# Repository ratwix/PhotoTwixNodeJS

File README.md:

PhotoTwixNodeJS
===============

A NodeJS Photobooth, that embedded a DSP RX1 printer (optional) for 2x6 strip

Backend : NodeJS
Frontend : CSS / Javascript.
Compatible browser : Chrome
User interface : Arduino

*Install*

- Install nodejs
- Install nodejs module :
-- Canvas (be sure to have GTK bin in your path)
-- Express
-- Gyp
-- Johnny-five
-- winreg
-- copysync
-- fs-extra
-- fs-tools
-- json
-- ncp
-- optimist
-- path
-- static
-- body-parser

*Run*

node server.js
In chrome : https://localhost:1443

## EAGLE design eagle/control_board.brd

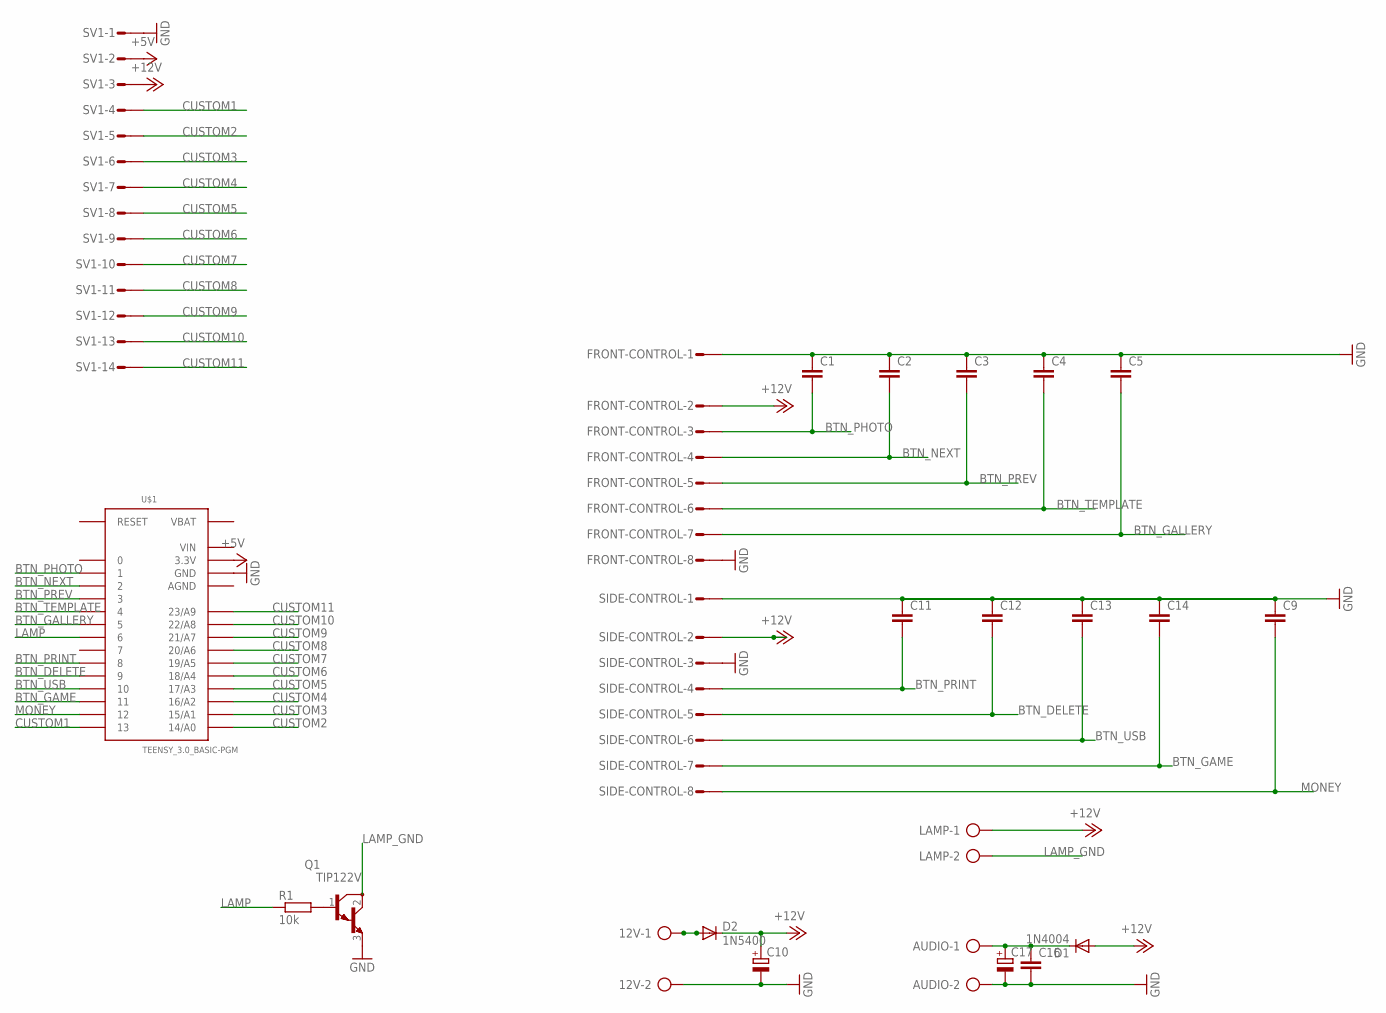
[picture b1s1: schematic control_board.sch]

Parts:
12V: AK300/2
AUDIO: AK300/2
C1, C2, C3, C4, C5, C9, C11, C12, C13, C14, C16: C-EU025-025X050; C025-025X050
C10: CPOL-EUE5-8.5; E5-8,5
C17: CPOL-EUE5-5; E5-5
D1: 1N4004; DO41-10
D2: 1N5400; DO201-15
FRONT-CONTROL: S08P
LAMP: AK300/2
Q1: TIP122V; TO220V
R1: 10k; 0204/7
SIDE-CONTROL: S08P
SV1: S14P
U$1: TEENSY_3.0_BASIC-PGM

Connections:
+5V: SV1.2, U$1.3.3V, U$1.3.3V1 (3.3V)
+12V: C10.+, D1.A, D2.C, FRONT-CONTROL.2, LAMP.1, SIDE-CONTROL.2, SV1.3
AGND: U$1.AGND
BTN_DELETE: C12.2, SIDE-CONTROL.5, U$1.9
BTN_GALLERY: C5.2, FRONT-CONTROL.7, U$1.5
BTN_GAME: C14.2, SIDE-CONTROL.7, U$1.11
BTN_NEXT: C2.2, FRONT-CONTROL.4, U$1.2
BTN_PHOTO: C1.2, FRONT-CONTROL.3, U$1.1
BTN_PREV: C3.2, FRONT-CONTROL.5, U$1.3
BTN_PRINT: C11.2, SIDE-CONTROL.4, U$1.8
BTN_TEMPLATE: C4.2, FRONT-CONTROL.6, U$1.4
BTN_USB: C13.2, SIDE-CONTROL.6, U$1.10
CUSTOM1: SV1.4, U$1.13
CUSTOM2: SV1.5, U$1.14/A0
CUSTOM3: SV1.6, U$1.15/A1
CUSTOM4: SV1.7, U$1.16/A2
CUSTOM5: SV1.8, U$1.17/A3
CUSTOM6: SV1.9, U$1.18/A4
CUSTOM7: SV1.10, U$1.19/A5
CUSTOM8: SV1.11, U$1.20/A6
CUSTOM9: SV1.12, U$1.21/A7
CUSTOM10: SV1.13, U$1.22/A8
CUSTOM11: SV1.14, U$1.23/A9
GND: 12V.2, AUDIO.2, C1.1, C2.1, C3.1, C4.1, C5.1, C9.1, C10.-, C11.1, C12.1, C13.1, C14.1, C16.2, C17.-, FRONT-CONTROL.1, FRONT-CONTROL.8, Q1.3 (E), SIDE-CONTROL.1, SIDE-CONTROL.3, SV1.1, U$1.GND, U$1.GND1 (GND)
LAMP: R1.1, U$1.6
LAMP_GND: LAMP.2, Q1.2 (C)
MONEY: C9.2, SIDE-CONTROL.8, U$1.12
unnamed: Q1.1 (B), R1.2
unnamed: AUDIO.1, C16.1, C17.+, D1.C
unnamed: 12V.1, D2.A
VBAT: U$1.VBAT
VIN: U$1.VIN

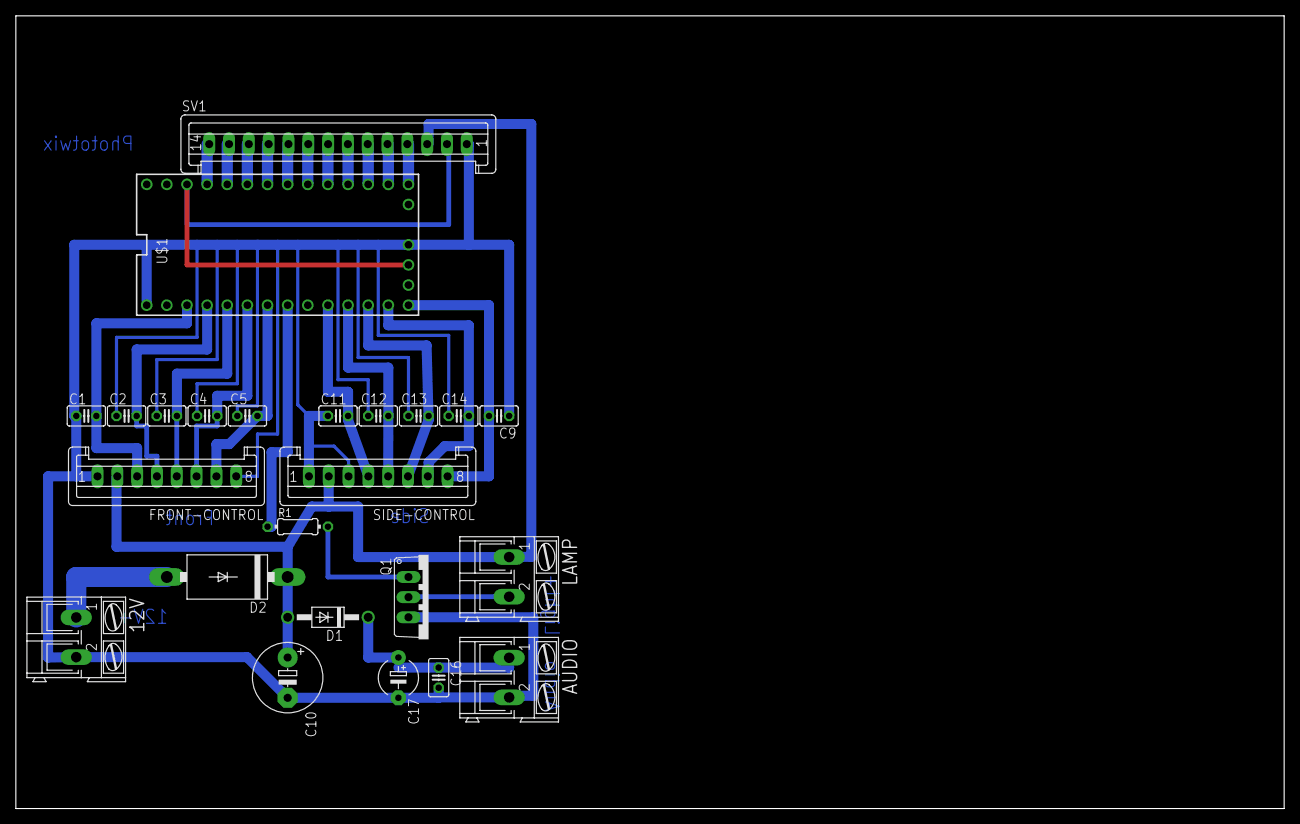
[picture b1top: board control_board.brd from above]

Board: 2 copper layers, 160.0 x 100.0 mm, 24 parts (0 on the bottom side), 29 nets.

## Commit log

2013-11-02 First arduino communication with johnny-five Cash acceptor Basic controller New gallery Saved parameter management
2013-11-03 Arduino pin
2013-11-12 Board & electronics
2013-11-13 Add USB copy + several bug fix
2013-11-14 Working form & light control
2013-11-22 Autocad plan
2013-11-27 Multiple bug fix. Review effects
2013-11-27 Add samples
2013-12-03 Change text
2013-12-16 v1.0
2014-02-02 bugfix usb
2014-04-01 Ajout de templates 1
2014-04-03 Template fonctionnel
2014-04-04 template editor ok
2014-04-04 Debug mode for non connected teensy optimisation frame rate & getContext('2D') useless call Correct template bug
2014-04-13 Template edition : sauvegarde et récupération de l'édition
2014-04-14 Use glfx for effects. Add 4 more effects
2014-04-14 Update library
2014-05-04 polices
2014-05-04 Fonts
2014-05-08 bug nb photos
2014-05-09 gallerie
2015-01-26 multiple changes
2015-01-26 ssl cert
2015-01-26 auto light
2015-04-11 Automatic create thumbnail
